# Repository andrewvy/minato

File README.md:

### minato

southpaw extended 75% layout keyboard, kailh MX sockets for hotswap functionality, using the Elite-C.

My first design, and a continuous work-in-progress.

---

- _2/9/2020:_ First revision boards sent for production.

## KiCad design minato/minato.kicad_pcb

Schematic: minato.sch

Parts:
C1, C3: 4.7nF; C_0805_2012Metric
C2: 10uF; C_0805_2012Metric
C6, C7, C8, C9, C10: 100nF; C_0805_2012Metric
C11: 10nF; C_0805_2012Metric
C12: 1uF; C_0805_2012Metric
D1, D2, D3, D4, D5, D6, D7, D8, D9, D10, D11, D12, D13, D14, D15, D16, D17, D18, D19, D20, D21, D22, D23, D24, D25, D26, D27, D28, D29, D30, D31, D32, D33, D34, D35, D36, D37, D38, D39, D40, D41, D42, D43, D44, D45, D46, D47, D48, D49, D50, D51, D52, D53, D54, D55, D56, D57, D58, D59, D60, D61, D62, D63, D64, D65, D66, D67, D68, D69, D70, D71, D72, D73, D74, D75, D76, D77, D78, D79, D80, D81, D82, D83, D84, D85, D86, D87, D88, D89, D90, D91, D92, D93, D94, D95, D96, D97, D98, D99, D100, D101, D102, D103, D104, D105, D106, D108: 1N4148; D_SOD123W_hand
F1: Polyfuse_Small; Fuse_1812_4532Metric
J1: Conn_ARM_JTAG_SWD_10; IDC-Header_2x05_P2.54mm_Vertical
J2: USB_C_Receptacle_USB2.0; USB_C_Receptacle_GCT_USB4085
MX0:0: Macro1; Kailh_socket_MX
MX0:1: Macro2; Kailh_socket_MX
MX0:2: NumLock; Kailh_socket_MX
MX0:3: /; Kailh_socket_MX
MX0:4: 7 / Home; Kailh_socket_MX
MX0:5: 8 / UpArrow; Kailh_socket_MX
MX0:6: 4 / LeftArrow; Kailh_socket_MX
MX0:7, MX4:3: 5; Kailh_socket_MX
MX0:8: 1 / End; Kailh_socket_MX
MX0:9: 2 / DownArrow; Kailh_socket_MX
MX0:10: 0 / Ins; Kailh_socket_MX
MX1:0: Macro3; Kailh_socket_MX
MX1:1: Macro4; Kailh_socket_MX
MX1:2: *; Kailh_socket_MX
MX1:3, MX7:3: -; Kailh_socket_MX
MX1:4: 9 / PgUp; Kailh_socket_MX
MX1:5, MX8:2: +; Kailh_socket_MX
MX1:6: 6 / RightArrow; Kailh_socket_MX
MX1:8: 3 / PgDn; Kailh_socket_MX
MX1:9: Enter; Kailh_socket_MX
MX1:11: . / Del; Kailh_socket_MX
MX2:0: Esc; Kailh_socket_MX
MX2:1: F1; Kailh_socket_MX
MX2:2: `; Kailh_socket_MX
MX2:3: 1; Kailh_socket_MX
MX2:4: Tab 1.5u; Kailh_socket_MX
MX2:6: Caps Lock 1.75u; Kailh_socket_MX
MX2:8: LeftShift 2.25u; Kailh_socket_MX
MX2:10: Ctrl 1.25u; Kailh_socket_MX
MX2:11: Win 1.25u; Kailh_socket_MX
MX3:0: F2; Kailh_socket_MX
MX3:1: F3; Kailh_socket_MX
MX3:2: 2; Kailh_socket_MX
MX3:3: 3; Kailh_socket_MX
MX3:4: W; Kailh_socket_MX
MX3:5: Q; Kailh_socket_MX
MX3:6: A; Kailh_socket_MX
MX3:7: S; Kailh_socket_MX
MX3:8: X; Kailh_socket_MX
MX3:9: Z; Kailh_socket_MX
MX3:10: Alt 1.25u; Kailh_socket_MX
MX3:11: Spacebar 6u; Kailh_socket_MX
MX4:0: F4; Kailh_socket_MX
MX4:1: F5; Kailh_socket_MX
MX4:2: 4; Kailh_socket_MX
MX4:4: R; Kailh_socket_MX
MX4:5: E; Kailh_socket_MX
MX4:6: D; Kailh_socket_MX
MX4:7: F; Kailh_socket_MX
MX4:8: V; Kailh_socket_MX
MX4:9: C; Kailh_socket_MX
MX5:0: F6; Kailh_socket_MX
MX5:1: F7; Kailh_socket_MX
MX5:2: 6; Kailh_socket_MX
MX5:3: 7; Kailh_socket_MX
MX5:4: Y; Kailh_socket_MX
MX5:5: T; Kailh_socket_MX
MX5:6: G; Kailh_socket_MX
MX5:7: H; Kailh_socket_MX
MX5:8: N; Kailh_socket_MX
MX5:9: B; Kailh_socket_MX
MX6:0: F8; Kailh_socket_MX
MX6:1: F9; Kailh_socket_MX
MX6:2: 8; Kailh_socket_MX
MX6:3: 9; Kailh_socket_MX
MX6:4: I; Kailh_socket_MX
MX6:5: U; Kailh_socket_MX
MX6:6: J; Kailh_socket_MX
MX6:7: K; Kailh_socket_MX
MX6:8: <; Kailh_socket_MX
MX6:9: M; Kailh_socket_MX
MX7:0: F10; Kailh_socket_MX
MX7:1: F11; Kailh_socket_MX
MX7:2: 0; Kailh_socket_MX
MX7:4: P; Kailh_socket_MX
MX7:5: O; Kailh_socket_MX
MX7:6: L; Kailh_socket_MX
MX7:7: :; Kailh_socket_MX
MX7:8: ?; Kailh_socket_MX
MX7:9: >; Kailh_socket_MX
MX7:10: Alt; Kailh_socket_MX
MX7:11: Fn; Kailh_socket_MX
MX8:0: F12; Kailh_socket_MX
MX8:1: PrtSc; Kailh_socket_MX
MX8:3: Backspace 2u; Kailh_socket_MX
MX8:4: }; Kailh_socket_MX
MX8:5: {; Kailh_socket_MX
MX8:6: \"; Kailh_socket_MX
MX8:7: RightEnter 2.25u; Kailh_socket_MX
MX8:9: RightShift 1.75u; Kailh_socket_MX
MX8:10: Ctrl; Kailh_socket_MX
MX8:11: LeftArrow; Kailh_socket_MX
MX9:0: Scroll Lock; Kailh_socket_MX
MX9:1: Pause; Kailh_socket_MX
MX9:2: Insert; Kailh_socket_MX
MX9:4: Delete; Kailh_socket_MX
MX9:5: | 1.5u; Kailh_socket_MX
MX9:6: Page Up; Kailh_socket_MX
MX9:8: UpArrow; Kailh_socket_MX
MX9:9: Page Down; Kailh_socket_MX
MX9:10: DownArrow; Kailh_socket_MX
MX9:11: RightArrow; Kailh_socket_MX
Q1: DTC123J; SOT-23
R1: 10k; R_2012
R2: 1M; R_2012
R3, R4: 5.1k; R_2012
SW1: SW_Push; SW_ALPS_SKRP
U1: MCP1700-3302E_SOT23; SOT-23
U2: STM32F103C8Tx; LQFP-48_7x7mm_P0.5mm
Y1: 16MHz; OSC_CSTCE16M0V53-R0

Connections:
3.3V: C7.1, C8.1, C9.1, C10.1, C11.1, C12.1, D108.2 (A), SW1.1, U1.2 (VO), U2.9 (VDDA), U2.24 (VDD), U2.36 (VDD), U2.48 (VDD)
5V: C6.1, D108.1 (K), F1.1, U1.3 (VI)
+3V3: J1.1 (VTref)
BOOT0: C2.2, D106.1 (K), R1.1, U2.44 (BOOT0)
Col0: D1.2 (A), D2.2 (A), D3.2 (A), D4.2 (A), D5.2 (A), D6.2 (A), D7.2 (A), D8.2 (A), D9.2 (A), D10.2 (A), D11.2 (A), D17.2 (A), U2.18 (PB0)
Col1: D12.2 (A), D13.2 (A), D14.2 (A), D15.2 (A), D16.2 (A), D18.2 (A), D19.2 (A), D20.2 (A), D21.2 (A), D25.2 (A), D27.2 (A), D30.2 (A), U2.19 (PB1)
Col2: D22.2 (A), D23.2 (A), D24.2 (A), D26.2 (A), D28.2 (A), D29.2 (A), D33.2 (A), D34.2 (A), D35.2 (A), D36.2 (A), D40.2 (A), D42.2 (A), U2.20 (PB2)
Col3: D31.2 (A), D32.2 (A), D37.2 (A), D38.2 (A), D39.2 (A), D41.2 (A), D45.2 (A), D46.2 (A), D47.2 (A), D51.2 (A), D78.2 (A), D84.2 (A), U2.39 (PB3)
Col4: D43.2 (A), D44.2 (A), D48.2 (A), D49.2 (A), D50.2 (A), D52.2 (A), D55.2 (A), D56.2 (A), D57.2 (A), D61.2 (A), D90.2 (A), D95.2 (A), U2.40 (PB4)
Col5: D53.2 (A), D54.2 (A), D58.2 (A), D59.2 (A), D60.2 (A), D62.2 (A), D65.2 (A), D66.2 (A), D67.2 (A), D71.2 (A), D99.2 (A), D105.2 (A), U2.41 (PB5)
Col6: D63.2 (A), D64.2 (A), D68.2 (A), D69.2 (A), D70.2 (A), D72.2 (A), D75.2 (A), D76.2 (A), D77.2 (A), D82.2 (A), U2.42 (PB6)
Col7: D73.2 (A), D74.2 (A), D79.2 (A), D80.2 (A), D81.2 (A), D83.2 (A), D87.2 (A), D88.2 (A), D89.2 (A), D94.2 (A), U2.43 (PB7)
Col8: D85.2 (A), D86.2 (A), D91.2 (A), D92.2 (A), D93.2 (A), D97.2 (A), D98.2 (A), D103.2 (A), D104.2 (A), U2.45 (PB8)
Col9: D96.2 (A), D100.2 (A), D101.2 (A), D102.2 (A), U2.46 (PB9)
DBUS+: J2.A6 (D+), J2.B6 (D+), U2.33 (PA12)
DBUS-: J2.A7 (D-), J2.B7 (D-), U2.32 (PA11)
NRST: C1.1, J1.10 (~RESET~), Q1.2 (E), U2.7 (NRST)
unnamed: C3.1, J2.S1 (SHIELD), R2.1
unnamed: D1.1 (K), MX0:0.1 (COL)
unnamed: D2.1 (K), MX0:2.1 (COL)
unnamed: D3.1 (K), MX0:4.1 (COL)
unnamed: D4.1 (K), MX0:6.1 (COL)
unnamed: D5.1 (K), MX0:8.1 (COL)
unnamed: D6.1 (K), MX0:10.1 (COL)
unnamed: D7.1 (K), MX0:1.1 (COL)
unnamed: D8.1 (K), MX0:3.1 (COL)
unnamed: D9.1 (K), MX0:5.1 (COL)
unnamed: D10.1 (K), MX0:7.1 (COL)
unnamed: D11.1 (K), MX0:9.1 (COL)
unnamed: D12.1 (K), MX1:0.1 (COL)
unnamed: D13.1 (K), MX1:2.1 (COL)
unnamed: D14.1 (K), MX1:4.1 (COL)
unnamed: D15.1 (K), MX1:6.1 (COL)
unnamed: D16.1 (K), MX1:8.1 (COL)
unnamed: D17.1 (K), MX1:11.1 (COL)
unnamed: D18.1 (K), MX1:1.1 (COL)
unnamed: D19.1 (K), MX1:3.1 (COL)
unnamed: D20.1 (K), MX1:5.1 (COL)
unnamed: D21.1 (K), MX1:9.1 (COL)
unnamed: D22.1 (K), MX2:0.1 (COL)
unnamed: D23.1 (K), MX2:2.1 (COL)
unnamed: D24.1 (K), MX2:4.1 (COL)
unnamed: D25.1 (K), MX2:6.1 (COL)
unnamed: D26.1 (K), MX2:8.1 (COL)
unnamed: D27.1 (K), MX2:10.1 (COL)
unnamed: D28.1 (K), MX2:1.1 (COL)
unnamed: D29.1 (K), MX2:3.1 (COL)
unnamed: D30.1 (K), MX2:11.1 (COL)
unnamed: D31.1 (K), MX3:0.1 (COL)
unnamed: D32.1 (K), MX3:2.1 (COL)
unnamed: D33.1 (K), MX3:5.1 (COL)
unnamed: D34.1 (K), MX3:6.1 (COL)
unnamed: D35.1 (K), MX3:9.1 (COL)
unnamed: D36.1 (K), MX3:10.1 (COL)
unnamed: D37.1 (K), MX3:1.1 (COL)
unnamed: D38.1 (K), MX3:3.1 (COL)
unnamed: D39.1 (K), MX3:4.1 (COL)
unnamed: D40.1 (K), MX3:7.1 (COL)
unnamed: D41.1 (K), MX3:8.1 (COL)
unnamed: D42.1 (K), MX3:11.1 (COL)
unnamed: D43.1 (K), MX4:0.1 (COL)
unnamed: D44.1 (K), MX4:2.1 (COL)
unnamed: D45.1 (K), MX4:5.1 (COL)
unnamed: D46.1 (K), MX4:6.1 (COL)
unnamed: D47.1 (K), MX4:9.1 (COL)
unnamed: D48.1 (K), MX4:1.1 (COL)
unnamed: D49.1 (K), MX4:3.1 (COL)
unnamed: D50.1 (K), MX4:4.1 (COL)
unnamed: D51.1 (K), MX4:7.1 (COL)
unnamed: D52.1 (K), MX4:8.1 (COL)
unnamed: D53.1 (K), MX5:0.1 (COL)
unnamed: D54.1 (K), MX5:2.1 (COL)
unnamed: D55.1 (K), MX5:5.1 (COL)
unnamed: D56.1 (K), MX5:6.1 (COL)
unnamed: D57.1 (K), MX5:9.1 (COL)
unnamed: D58.1 (K), MX5:1.1 (COL)
unnamed: D59.1 (K), MX5:3.1 (COL)
unnamed: D60.1 (K), MX5:4.1 (COL)
unnamed: D61.1 (K), MX5:7.1 (COL)
unnamed: D62.1 (K), MX5:8.1 (COL)
unnamed: D63.1 (K), MX6:0.1 (COL)
unnamed: D64.1 (K), MX6:2.1 (COL)
unnamed: D65.1 (K), MX6:5.1 (COL)
unnamed: D66.1 (K), MX6:6.1 (COL)
unnamed: D67.1 (K), MX6:9.1 (COL)
unnamed: D68.1 (K), MX6:1.1 (COL)
unnamed: D69.1 (K), MX6:3.1 (COL)
unnamed: D70.1 (K), MX6:4.1 (COL)
unnamed: D71.1 (K), MX6:7.1 (COL)
unnamed: D72.1 (K), MX6:8.1 (COL)
unnamed: D73.1 (K), MX7:0.1 (COL)
unnamed: D74.1 (K), MX7:2.1 (COL)
unnamed: D75.1 (K), MX7:5.1 (COL)
unnamed: D76.1 (K), MX7:6.1 (COL)
unnamed: D77.1 (K), MX7:9.1 (COL)
unnamed: D78.1 (K), MX7:10.1 (COL)
unnamed: D79.1 (K), MX7:1.1 (COL)
unnamed: D80.1 (K), MX7:3.1 (COL)
unnamed: D81.1 (K), MX7:4.1 (COL)
unnamed: D82.1 (K), MX7:7.1 (COL)
unnamed: D83.1 (K), MX7:8.1 (COL)
unnamed: D84.1 (K), MX7:11.1 (COL)
unnamed: D85.1 (K), MX8:0.1 (COL)
unnamed: D86.1 (K), MX8:2.1 (COL)
unnamed: D87.1 (K), MX8:5.1 (COL)
unnamed: D88.1 (K), MX8:6.1 (COL)
unnamed: D89.1 (K), MX8:9.1 (COL)
unnamed: D90.1 (K), MX8:10.1 (COL)
unnamed: D91.1 (K), MX8:1.1 (COL)
unnamed: D92.1 (K), MX8:3.1 (COL)
unnamed: D93.1 (K), MX8:4.1 (COL)
unnamed: D94.1 (K), MX8:7.1 (COL)
unnamed: D95.1 (K), MX8:11.1 (COL)
unnamed: D96.1 (K), MX9:0.1 (COL)
unnamed: D97.1 (K), MX9:5.1 (COL)
unnamed: D98.1 (K), MX9:8.1 (COL)
unnamed: D99.1 (K), MX9:10.1 (COL)
unnamed: D100.1 (K), MX9:1.1 (COL)
unnamed: D101.1 (K), MX9:2.1 (COL)
unnamed: D102.1 (K), MX9:4.1 (COL)
unnamed: D103.1 (K), MX9:6.1 (COL)
unnamed: D104.1 (K), MX9:9.1 (COL)
unnamed: D105.1 (K), MX9:11.1 (COL)
unnamed: D106.2 (A), Q1.1 (B), SW1.2
unnamed: J2.A5 (CC1), R3.2
unnamed: J2.B5 (CC2), R4.2
Row0: MX0:0.2 (ROW), MX1:0.2 (ROW), MX2:0.2 (ROW), MX3:0.2 (ROW), MX4:0.2 (ROW), MX5:0.2 (ROW), MX6:0.2 (ROW), MX7:0.2 (ROW), MX8:0.2 (ROW), MX9:0.2 (ROW), U2.21 (PB10)
Row1: MX0:1.2 (ROW), MX1:1.2 (ROW), MX2:1.2 (ROW), MX3:1.2 (ROW), MX4:1.2 (ROW), MX5:1.2 (ROW), MX6:1.2 (ROW), MX7:1.2 (ROW), MX8:1.2 (ROW), MX9:1.2 (ROW), U2.22 (PB11)
Row2: MX0:2.2 (ROW), MX1:2.2 (ROW), MX2:2.2 (ROW), MX3:2.2 (ROW), MX4:2.2 (ROW), MX5:2.2 (ROW), MX6:2.2 (ROW), MX7:2.2 (ROW), MX8:2.2 (ROW), MX9:2.2 (ROW), U2.25 (PB12)
Row3: MX0:3.2 (ROW), MX1:3.2 (ROW), MX2:3.2 (ROW), MX3:3.2 (ROW), MX4:3.2 (ROW), MX5:3.2 (ROW), MX6:3.2 (ROW), MX7:3.2 (ROW), MX8:3.2 (ROW), U2.26 (PB13)
Row4: MX0:4.2 (ROW), MX1:4.2 (ROW), MX2:4.2 (ROW), MX3:4.2 (ROW), MX4:4.2 (ROW), MX5:4.2 (ROW), MX6:4.2 (ROW), MX7:4.2 (ROW), MX8:4.2 (ROW), MX9:4.2 (ROW), U2.27 (PB14)
Row5: MX0:5.2 (ROW), MX1:5.2 (ROW), MX3:5.2 (ROW), MX4:5.2 (ROW), MX5:5.2 (ROW), MX6:5.2 (ROW), MX7:5.2 (ROW), MX8:5.2 (ROW), MX9:5.2 (ROW), U2.28 (PB15)
Row6: MX0:6.2 (ROW), MX1:6.2 (ROW), MX3:6.2 (ROW), MX4:6.2 (ROW), MX5:6.2 (ROW), MX6:6.2 (ROW), MX7:6.2 (ROW), MX8:6.2 (ROW), MX9:6.2 (ROW), U2.15 (PA5)
Row7: MX0:7.2 (ROW), MX2:6.2 (ROW), MX3:7.2 (ROW), MX4:7.2 (ROW), MX5:7.2 (ROW), MX6:7.2 (ROW), MX7:7.2 (ROW), MX8:7.2 (ROW), U2.14 (PA4)
Row8: MX0:8.2 (ROW), MX1:8.2 (ROW), MX2:8.2 (ROW), MX3:8.2 (ROW), MX4:8.2 (ROW), MX5:8.2 (ROW), MX6:8.2 (ROW), MX7:8.2 (ROW), MX9:8.2 (ROW), U2.13 (PA3)
Row9: MX0:9.2 (ROW), MX1:9.2 (ROW), MX3:9.2 (ROW), MX4:9.2 (ROW), MX5:9.2 (ROW), MX6:9.2 (ROW), MX7:9.2 (ROW), MX8:9.2 (ROW), MX9:9.2 (ROW), U2.12 (PA2)
Row10: MX0:10.2 (ROW), MX2:10.2 (ROW), MX3:10.2 (ROW), MX7:10.2 (ROW), MX8:10.2 (ROW), MX9:10.2 (ROW), U2.11 (PA1)
Row11: MX1:11.2 (ROW), MX2:11.2 (ROW), MX3:11.2 (ROW), MX7:11.2 (ROW), MX8:11.2 (ROW), MX9:11.2 (ROW), U2.10 (PA0)
SWCLK: J1.4 (SWDCLK/TCK), U2.37 (PA14)
SWDIO: J1.2 (SWDIO/TMS), U2.34 (PA13)
VBUS: F1.2, J2.A4 (VBUS), J2.A9 (VBUS), J2.B4 (VBUS), J2.B9 (VBUS)
VSS1: C1.2, C2.1, C3.2, C6.2, C7.2, C8.2, C9.2, C10.2, C11.2, C12.2, J1.3 (GND), J1.5 (GND), J1.9 (GNDDetect), J2.A1 (GND), J2.A12 (GND), J2.B1 (GND), J2.B12 (GND), Q1.3 (C), R1.2, R2.2, R3.1, R4.1, U1.1 (GND), U2.1 (VBAT), U2.8 (VSSA), U2.23 (VSS), U2.35 (VSS), U2.47 (VSS), Y1.2 (GND)
XTI: U2.3 (PC14), Y1.1 (IN)
XTO: U2.4 (PC15), Y1.3 (OUT)

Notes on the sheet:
JTAG Interface
Keyboard Matrix
16MHz Oscillator
Hardware Reset
Decoupling capacitors
USB C Receptacle
Power Supply

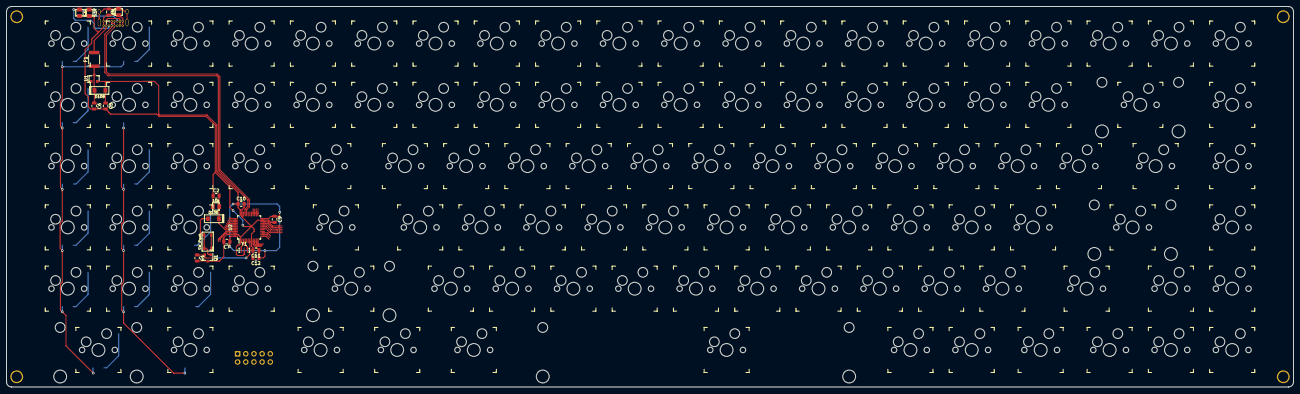
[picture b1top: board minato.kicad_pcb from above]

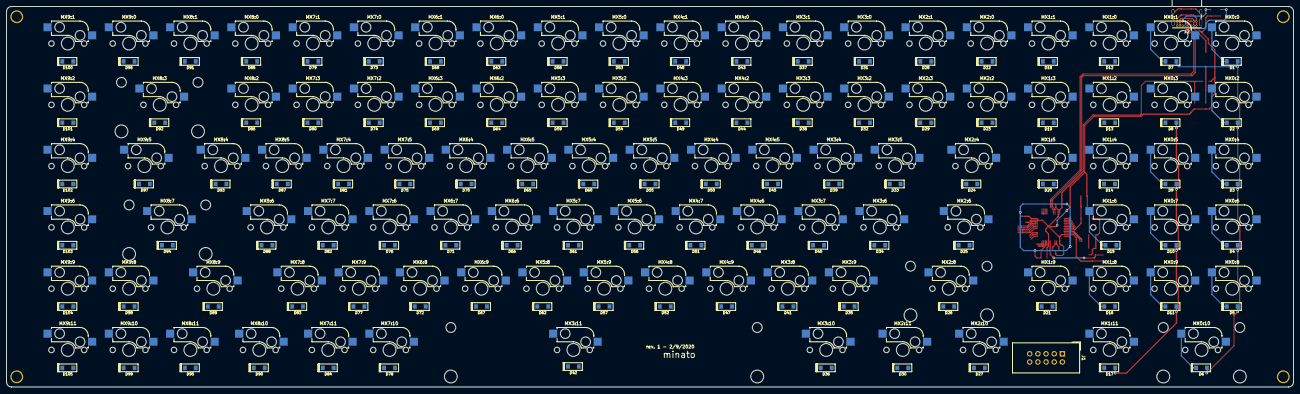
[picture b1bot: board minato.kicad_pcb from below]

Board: 2 copper layers, 400.1 x 118.3 mm, 238 parts (107 on the bottom side), 143 nets.

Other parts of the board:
HOLE_M3, HOLE_M3#2, HOLE_M3#3, HOLE_M3#4: VAL**; HOLE_M3

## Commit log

2020-02-10 :tada: Initial keyboard matrix single + duplex
2020-02-10 :sparkles: Rev. 2 Routing
2020-02-10 :sparkles: Layout basic keyboard switches
2020-02-10 :tada: Rev 1 initial design complete
2020-02-10 :sparkles: Add global labels
2020-02-10 :sparkles: Name reference switches
2020-02-10 :sparkles: Add stabilizers
2020-02-10 :sparkles: Rev. 1 Routing
2020-02-10 :sparkles: Map schematics to footprints
2020-02-10 :sparkles: Revamp stabilizers
2020-02-11 :tada: Rev. 1 production
2020-02-13 :construction: Add STM32F103 schematic
2020-02-13 :bug: Fix submodules
2020-02-13 :sparkles: Add crystal + HW reset
2020-02-13 :sparkles: Add decoupler
2020-02-13 :sparkles: Add USB-C receptacle
2020-02-14 :sparkles: Assign footprints
2020-02-14 :construction: WIP
2020-02-15 :construction: More PCB work
2020-02-16 :sparkles: Place components on PCB
2020-02-16 :sparkles: Wire up USB-C receptacle
